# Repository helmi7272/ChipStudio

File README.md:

# ChipStudio
Графический инструмент проектирования ChipStudio. Новинки собственного производства Чип и Дип. 

Вам не хватает выводов GPIO для управления алгоритмами DSP, собранными в SigmaStudio? Или вы хотите, чтобы ресурсы звукового процессора не распылялись на кнопки, слайдеры или переключатели, а были сконцентрированы только на цифровой обработке аудио? А, может, мечтаете об одновременном управлении несколькими звуковыми процессорами и регулировке FIR-фильтров на лету? 
Обратите внимание на CHIP Studio!  
Интегрированная среда разработки CHIP Studio. Позволяет инженерам без опыта или с небольшим опытом написания программ для DSP процессоров добавлять любые функции внешней регулировки в свои проекты цифровой обработки сигналов. Это могут быть потенциометры, кнопки и переключатели.
CHIP Studio поддерживает все модули RDC2-0027, собранные на SigmaDSP процессоре ADAU1701, а также модуль SigmaDSP ADAU1761.
Этот инструмент поможет пользователям сократить время проектирования без ухудшения качества или характеристик.
Модуль RDC2-0051 предназначен для простого подключения внешних органов управления к проектам цифровой обработки звука созданных в <strong><em>Sigma Studio </em></strong>&ndash; среде разработки от компании Analog Devices. Код для любых функций модуля управления разрабатывается с помощью графического инструмента программирования <strong><em>CHIP Studio</em></strong>.<br />
Интегрированная среда разработки <strong><em>CHIP Studio </em></strong>v 0.0. Позволяет инженерам без опыта или с небольшим опытом написания программ для DSP процессоров добавлять любые функции внешней регулировки в свои проекты цифровой обработки сигналов. Это могут быть &nbsp;потенциометры, кнопки и переключатели.<br />
<strong><em>CHIP Studio </em></strong>поддерживает все модули RDC2-0027 собранные на SigmaDSP процессоре ADAU1701 и модуль SigmaDSP ADAU1761.<br />
Этот инструмент поможет пользователям сократить время проектирования без ухудшения качества или характеристик.<br />
<br />

<h2>Технические характеристики</h2>
Шины для управления DSP:<br />
<em>I2C x 2, SPI x 2</em><br />
Линий ввода/вывода&nbsp;- 10<br />
Функции линий ввода / вывода:<br />
<em>Кнопки/переключатели - 10</em><br />
<em>Переменные резисторы - 6</em><br />
На плате установлены:<br />
<em>Переменные резисторы &ndash; 2<br />
Кнопки &ndash; 2</em><br />
Питание &ndash; 5В внешнее или USB<br />
Размер платы: 100 мм х 34 мм
<h2>Схема</h2>
<p></p>

<h2>Назначение разъемов</h2>

<p></p>

<h2>Подключение ADAU1761</h2>
<p></p>
<h2>Подключение ADAU1701</h2>
<p></p>

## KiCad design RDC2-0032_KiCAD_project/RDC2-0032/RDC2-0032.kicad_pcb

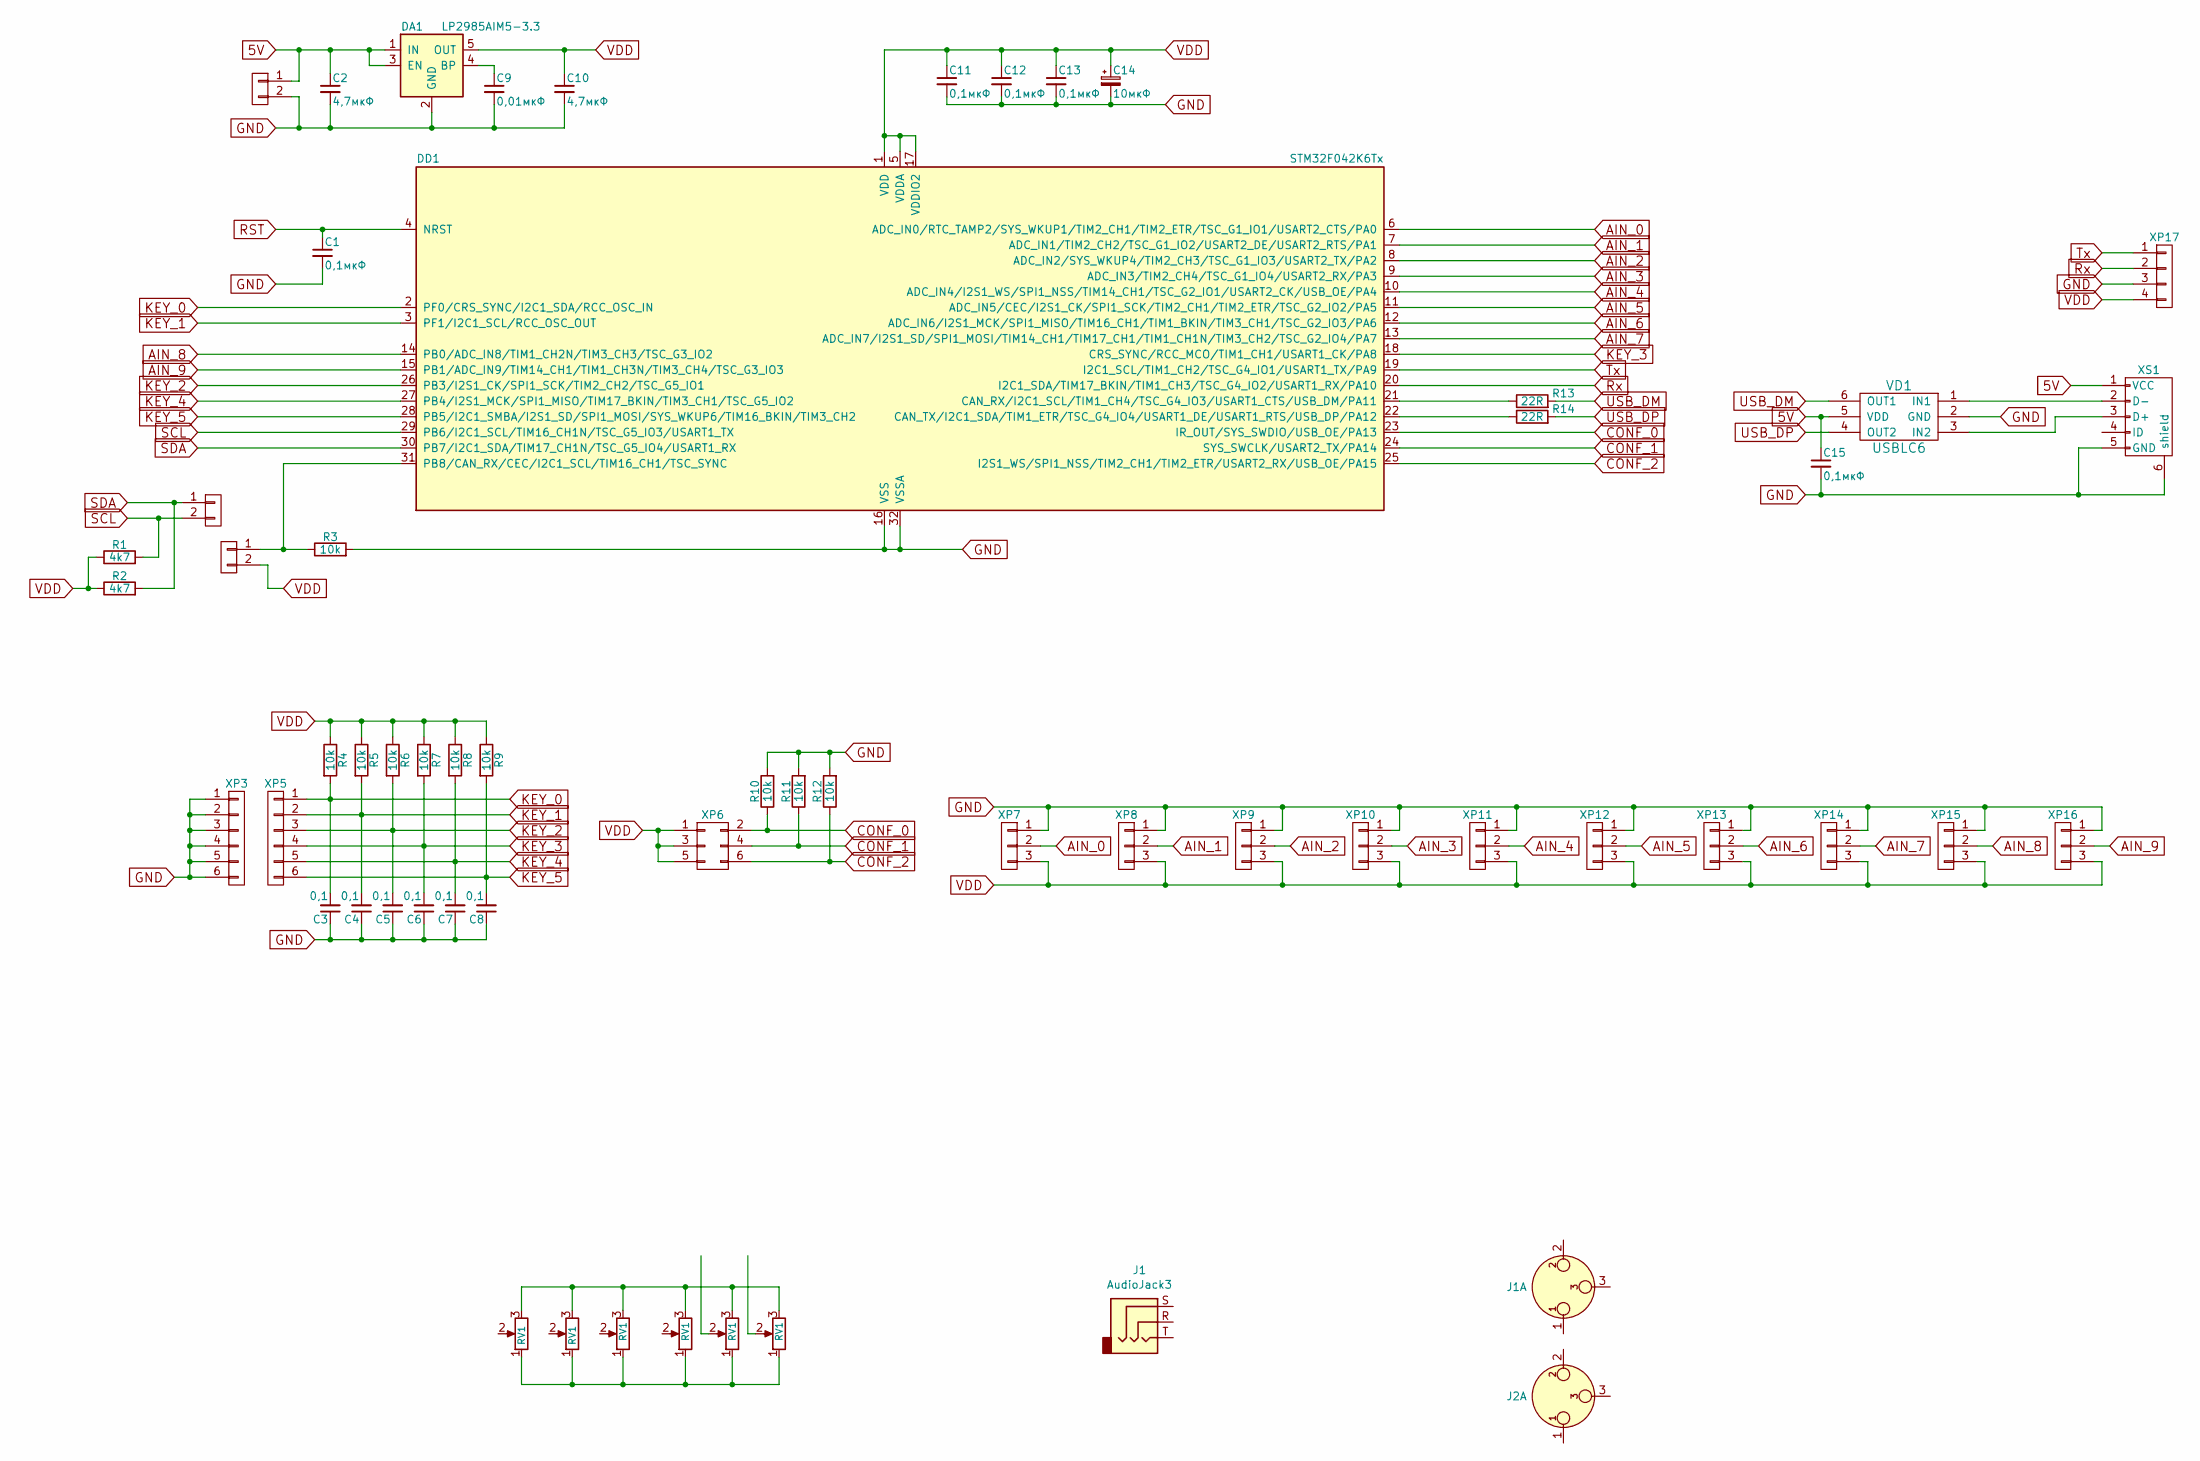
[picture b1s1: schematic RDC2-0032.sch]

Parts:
C1, C11, C12, C13, C15: 0,1мкФ; C_0603_HandSoldering
C2, C10: 4,7мкФ; C_0603_HandSoldering
C3, C4, C5, C6, C7, C8: 0,1; C_0603_HandSoldering
C9: 0,01мкФ; C_0603_HandSoldering
C14: 10мкФ; TantalC_SizeA_EIA-3216_HandSoldering_mm
DA1: LP2985AIM5-3.3; SOT-23-5_mm
DD1: STM32F042K6Tx; TQFP-32_7x7mm_Pitch0.8mm
J1: AudioJack3
J2: XLR3_AudioJack2_Combo
R1, R2: 4k7; R_0603_HandSoldering
R3, R4, R5, R6, R7, R8, R9, R10, R11, R12: 10k; R_0603_HandSoldering
R13, R14: 22R; R_0603_HandSoldering
VD1: USBLC6; SOT23-6L
XP1, XP2, XP4: PLS-2; Pin_Header_Straight_1x02_mm
XP3, XP5: CONN_01X06; Pin_Header_Straight_1x06_mm
XP6: CONN_02X03; Pin_Header_Straight_2x03_mm
XP7, XP8, XP9, XP10, XP11, XP12, XP13, XP14, XP15, XP16: CONN_01X03; Pin_Header_Straight_1x03_mm
XP17: CONN_01X04; Pin_Header_Straight_1x04_mm
XS1: USB_OTG; USB_Mini-B_mm

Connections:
5V: C2.1, C15.1, DA1.1 (IN), DA1.3 (EN), VD1.5 (VDD), XP4.1, XS1.1 (VCC)
AIN_0: DD1.6 (ADC_IN0/RTC_TAMP2/SYS_WKUP1/TIM2_CH1/TI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), XP7.2
AIN_1: DD1.7 (ADC_IN1/TIM2_CH2/TSC_G1_IO2/USART2_DE/U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), XP8.2
AIN_2: DD1.8 (ADC_IN2/SYS_WKUP4/TIM2_CH3/TSC_G1_IO3/U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), XP9.2
AIN_3: DD1.9 (ADC_IN3/TIM2_CH4/TSC_G1_IO4/USART2_RX/P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), XP10.2
AIN_4: DD1.10 (ADC_IN4/I2S1_WS/SPI1_NSS/TIM14_CH1/TSC_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), XP11.2
AIN_5: DD1.11 (ADC_IN5/CEC/I2S1_CK/SPI1_SCK/TIM2_CH1/T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), XP12.2
AIN_6: DD1.12 (ADC_IN6/I2S1_MCK/SPI1_MISO/TIM16_CH1/TI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), XP13.2
AIN_7: DD1.13 (ADC_IN7/I2S1_SD/SPI1_MOSI/TIM14_CH1/TIM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), XP14.2
AIN_8: DD1.14 (PB0/ADC_IN8/TIM1_CH2N/TIM3_CH3/TSC_G3_I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), XP15.2
AIN_9: DD1.15 (PB1/ADC_IN9/TIM14_CH1/TIM1_CH3N/TIM3_CH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), XP16.2
CONF_0: DD1.23 (IR_OUT/SYS_SWDIO/USB_OE/PA13), R10.1, XP6.2
CONF_1: DD1.24 (SYS_SWCLK/USART2_TX/PA14), R11.1, XP6.4
CONF_2: DD1.25 (I2S1_WS/SPI1_NSS/TIM2_CH1/TIM2_ETR/USAR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), R12.1, XP6.6
GND: C1.2, C2.2, C3.1, C4.1, C5.1, C6.1, C7.1, C8.1, C9.2, C10.2, C11.2, C12.2, C13.2, C14.2, C15.2, DA1.2 (GND), DD1.16 (VSS), DD1.32 (VSSA), R3.2, R10.2, R11.2, R12.2, VD1.2 (GND), XP3.1, XP3.2, XP3.3, XP3.4, XP3.5, XP3.6, XP4.2, XP7.1, XP8.1, XP9.1, XP10.1, XP11.1, XP12.1, XP13.1, XP14.1, XP15.1, XP16.1, XP17.3, XS1.5 (GND), XS1.6 (shield)
KEY_0: C3.2, DD1.2 (PF0/CRS_SYNC/I2C1_SDA/RCC_OSC_IN), R4.2, XP5.1
KEY_1: C4.2, DD1.3 (PF1/I2C1_SCL/RCC_OSC_OUT), R5.2, XP5.2
KEY_2: C5.2, DD1.26 (PB3/I2S1_CK/SPI1_SCK/TIM2_CH2/TSC_G5_IO1), R6.2, XP5.3
KEY_3: C6.2, DD1.18 (CRS_SYNC/RCC_MCO/TIM1_CH1/USART1_CK/PA8), R7.2, XP5.4
KEY_4: C7.2, DD1.27 (PB4/I2S1_MCK/SPI1_MISO/TIM17_BKIN/TIM3_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), R8.2, XP5.5
KEY_5: C8.2, DD1.28 (PB5/I2C1_SMBA/I2S1_SD/SPI1_MOSI/SYS_WKU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), R9.2, XP5.6
unnamed: C9.1, DA1.4 (BP)
unnamed: DD1.21 (CAN_RX/I2C1_SCL/TIM1_CH4/TSC_G4_IO3/USA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), R13.1
unnamed: DD1.22 (CAN_TX/I2C1_SDA/TIM1_ETR/TSC_G4_IO4/USA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), R14.1
unnamed: DD1.31 (PB8/CAN_RX/CEC/I2C1_SCL/TIM16_CH1/TSC_S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), R3.1, XP2.1
unnamed: VD1.1 (IN1), XS1.2 (D-)
unnamed: VD1.3 (IN2), XS1.3 (D+)
RST: C1.1, DD1.4 (NRST)
Rx: DD1.20 (I2C1_SDA/TIM17_BKIN/TIM1_CH3/TSC_G4_IO2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), XP17.2
SCL: DD1.29 (PB6/I2C1_SCL/TIM16_CH1N/TSC_G5_IO3/USAR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), R1.2, XP1.2
SDA: DD1.30 (PB7/I2C1_SDA/TIM17_CH1N/TSC_G5_IO4/USAR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), R2.2, XP1.1
Tx: DD1.19 (I2C1_SCL/TIM1_CH2/TSC_G4_IO1/USART1_TX/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), XP17.1
USB_DM: R13.2, VD1.6 (OUT1)
USB_DP: R14.2, VD1.4 (OUT2)
VDD: C10.1, C11.1, C12.1, C13.1, C14.1, DA1.5 (OUT), DD1.1 (VDD), DD1.5 (VDDA), DD1.17 (VDDIO2), R1.1, R2.1, R4.1, R5.1, R6.1, R7.1, R8.1, R9.1, XP2.2, XP6.1, XP6.3, XP6.5, XP7.3, XP8.3, XP9.3, XP10.3, XP11.3, XP12.3, XP13.3, XP14.3, XP15.3, XP16.3, XP17.4

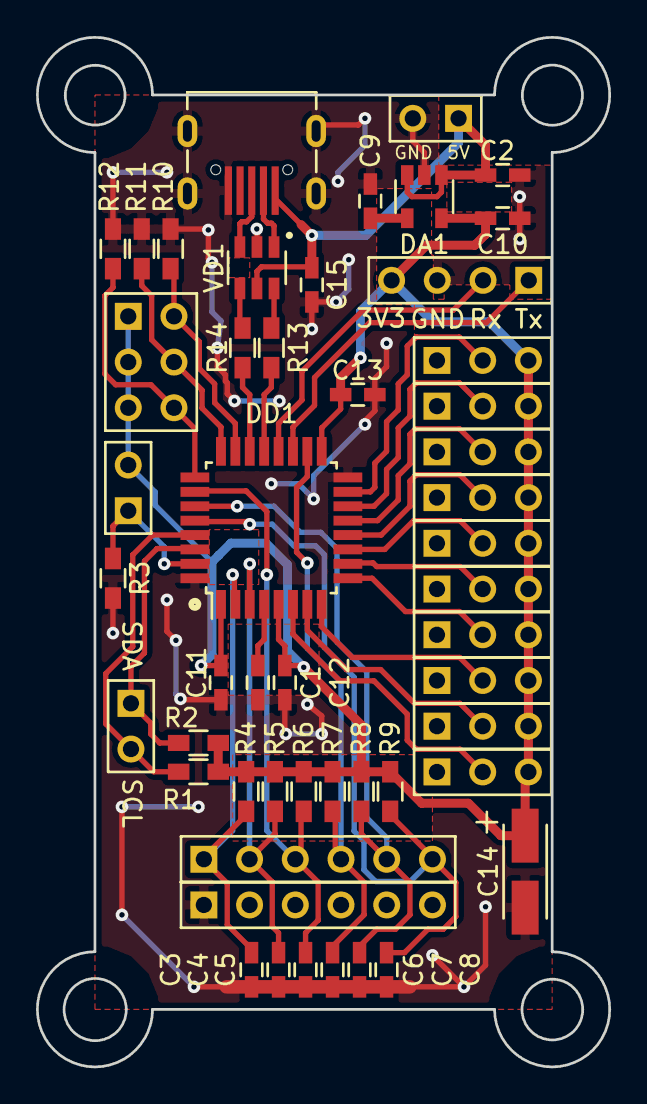
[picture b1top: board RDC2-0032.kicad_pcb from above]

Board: 2 copper layers, 31.8 x 57.2 mm, 50 parts (0 on the bottom side), 35 nets.

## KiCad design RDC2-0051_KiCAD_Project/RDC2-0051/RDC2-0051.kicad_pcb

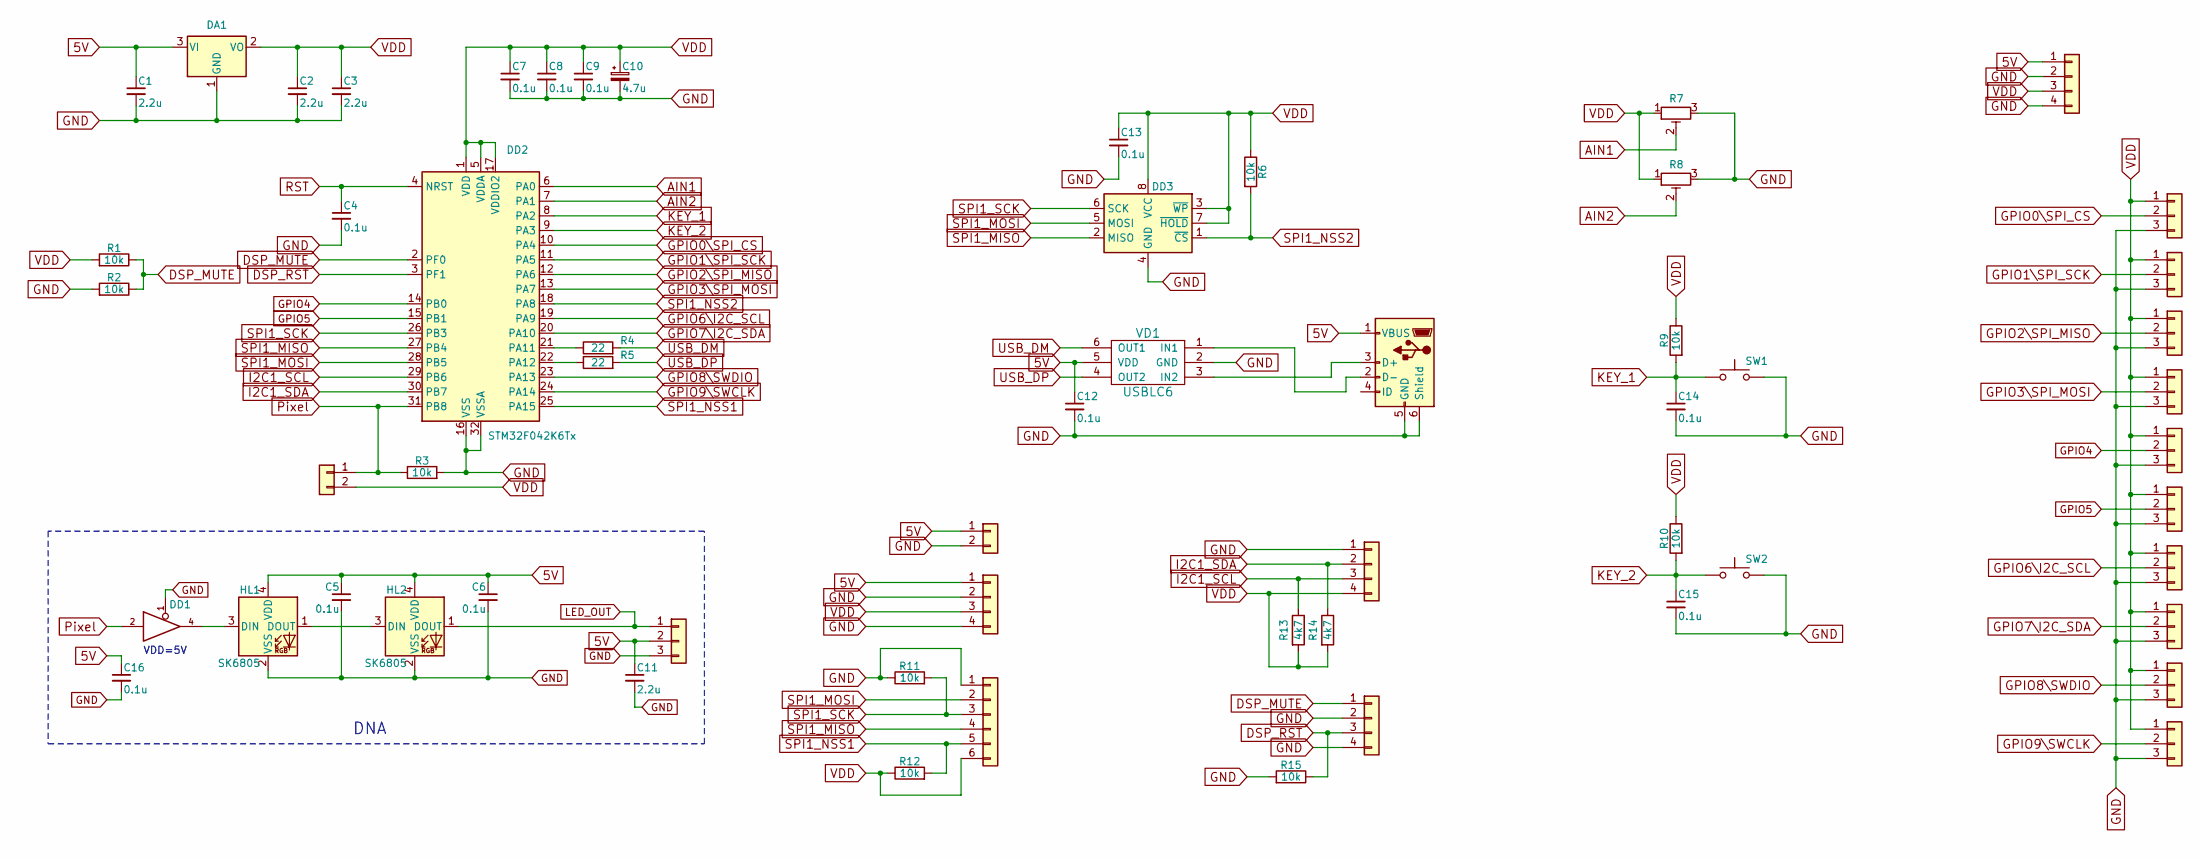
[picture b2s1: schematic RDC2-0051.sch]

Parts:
C1, C2, C3, C11: 2.2u; C_0603_HandSoldering
C4, C5, C6, C7, C8, C9, C12, C13, C14, C15, C16: 0.1u; C_0603_HandSoldering
C10: 4.7u; TantalC_SizeA_EIA-3216_mm
DA1: LM1117-3.3; SOT-223
DD1: 74AHC1G125; SOT-23-5_mm
DD2: STM32F042K6Tx; LQFP-32_7x7mm_Pitch0.8mm
DD3: 25LCxxx; SOIC-8_combo_Pitch1.27mm
HL1, HL2: SK6805; LED_SK6805_PLCC4_2.4x2.7mm_P1.3mm
R1, R2, R3, R6, R9, R10, R11, R12, R15: 10k; R_0603
R4, R5: 22; R_0603
R7, R8: R_POT_TRIM; R0904N
R13, R14: 4k7; R_0603
SW1, SW2: SW_PUSH; SW_PUSH_6mm_H13mm
VD1: USBLC6; SOT23-6L
XP1, XP3: Conn_01x02; Pin_Header_Straight_1x02_mm
XP2, XP11, XP12, XP13, XP14, XP15, XP16, XP17, XP18, XP19, XP20: Conn_01x03; Pin_Header_Straight_1x03_mm
XP4, XP6, XP7, XP8: Conn_01x04; Pin_Header_Straight_1x04_mm
XP5: Conn_01x06; Pin_Header_Straight_1x06_mm
XS1: USB_B_Micro; USB_micro_Molex_47346-0001

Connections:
5V: C1.1, C5.1, C6.1, C11.1, C12.1, C16.1, DA1.3 (VI), DD1.5 (VCC), HL1.4 (VDD), HL2.4 (VDD), VD1.5 (VDD), XP2.2, XP3.1, XP4.1, XP8.1, XS1.1 (VBUS)
AIN1: DD2.6 (PA0), R7.2
AIN2: DD2.7 (PA1), R8.2
DSP_MUTE: DD2.2 (PF0), R1.1, R2.1, XP7.1
DSP_RST: DD2.3 (PF1), R15.1, XP7.3
GND: C1.2, C2.2, C3.2, C4.2, C5.2, C6.2, C7.2, C8.2, C9.2, C10.2, C11.2, C12.2, C13.2, C14.2, C15.2, C16.2, DA1.1 (GND), DD1.1, DD1.3 (GND), DD2.16 (VSS), DD2.32 (VSSA), DD3.4 (GND), HL1.2 (VSS), HL2.2 (VSS), R2.2, R3.2, R7.3, R7.4, R8.3, R8.4, R11.1, R15.2, SW1.2, SW2.2, VD1.2 (GND), XP2.3, XP3.2, XP4.2, XP4.4, XP5.1, XP6.1, XP7.2, XP7.4, XP8.2, XP8.4, XP11.3, XP12.3, XP13.3, XP14.3, XP15.3, XP16.3, XP17.3, XP18.3, XP19.3, XP20.3, XS1.5 (GND), XS1.6 (Shield)
GPIO0\SPI_CS: DD2.10 (PA4), XP11.2
GPIO1\SPI_SCK: DD2.11 (PA5), XP12.2
GPIO2\SPI_MISO: DD2.12 (PA6), XP13.2
GPIO3\SPI_MOSI: DD2.13 (PA7), XP14.2
GPIO4: DD2.14 (PB0), XP15.2
GPIO5: DD2.15 (PB1), XP16.2
GPIO6\I2C_SCL: DD2.19 (PA9), XP17.2
GPIO7\I2C_SDA: DD2.20 (PA10), XP18.2
GPIO8\SWDIO: DD2.23 (PA13), XP19.2
GPIO9\SWCLK: DD2.24 (PA14), XP20.2
I2C1_SCL: DD2.29 (PB6), R13.1, XP6.3
I2C1_SDA: DD2.30 (PB7), R14.1, XP6.2
KEY_1: C14.1, DD2.8 (PA2), R9.2, SW1.1
KEY_2: C15.1, DD2.9 (PA3), R10.2, SW2.1
LED_OUT: HL2.1 (DOUT), XP2.1
unnamed: DD1.4, HL1.3 (DIN)
unnamed: DD2.21 (PA11), R4.1
unnamed: DD2.22 (PA12), R5.1
unnamed: HL1.1 (DOUT), HL2.3 (DIN)
unnamed: VD1.1 (IN1), XS1.2 (D-)
unnamed: VD1.3 (IN2), XS1.3 (D+)
Pixel: DD1.2, DD2.31 (PB8), R3.1, XP1.1
RST: C4.1, DD2.4 (NRST)
SPI1_MISO: DD2.27 (PB4), DD3.2 (MISO), XP5.4
SPI1_MOSI: DD2.28 (PB5), DD3.5 (MOSI), XP5.2
SPI1_NSS1: DD2.25 (PA15), R12.2, XP5.5
SPI1_NSS2: DD2.18 (PA8), DD3.1 (~CS), R6.2
SPI1_SCK: DD2.26 (PB3), DD3.6 (SCK), R11.2, XP5.3
USB_DM: R4.2, VD1.6 (OUT1)
USB_DP: R5.2, VD1.4 (OUT2)
VDD: C2.1, C3.1, C7.1, C8.1, C9.1, C10.1, C13.1, DA1.2 (VO), DA1.4, DD2.1 (VDD), DD2.5 (VDDA), DD2.17 (VDDIO2), DD3.3 (~WP), DD3.7 (~HOLD), DD3.8 (VCC), R1.2, R6.1, R7.1, R8.1, R9.1, R10.1, R12.1, R13.2, R14.2, XP1.2, XP4.3, XP5.6, XP6.4, XP8.3, XP11.1, XP12.1, XP13.1, XP14.1, XP15.1, XP16.1, XP17.1, XP18.1, XP19.1, XP20.1

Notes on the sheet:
VDD=5V
DNA

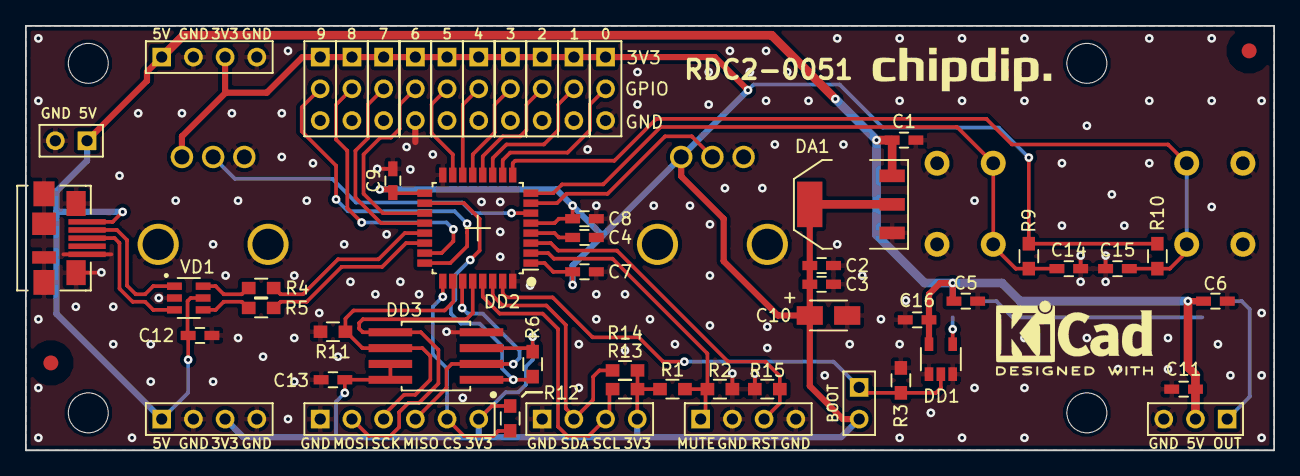
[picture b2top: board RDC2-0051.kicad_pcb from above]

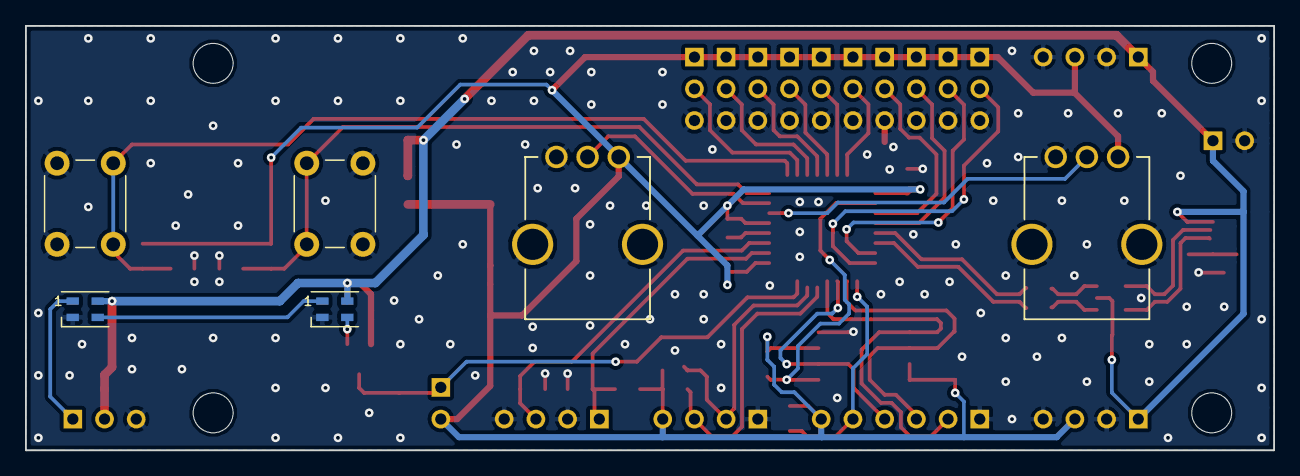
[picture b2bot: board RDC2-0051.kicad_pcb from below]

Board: 2 copper layers, 100.0 x 34.0 mm, 59 parts (6 on the bottom side), 37 nets.

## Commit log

2020-03-20 ADAU1761 ChipStudio project Vol, Bal, Mute, SuperB
2020-03-20 ChipStudio soft v3.0
2020-03-20 RDC2-0051 KiCAD project
2020-03-20 IAR Project
2020-03-20 firmware DFU v0.2
2020-03-20 FirmWare DFU
2020-03-27 ChipStudio soft v4.0
2020-03-27 firmware DFU v0.4
2020-03-27 ADAU1761 Vol, Bal, Mute, SuperB, Timbre
2020-04-04 firmware DFU v0.5
    v0.5
    - добавлена поддержка RDC2-0050 (TAS3251)
    - добавлена поддержка блоков схемы SigmaStudio, занимающих в памяти параметров DSP более 63 адресов (например, FIR-фильтры)
    - исправлена ошибка управления несколькими блоками DSP,
    подключенными к одной линии
2020-04-04 ChipStudio soft v5.0
    v0.5
    - добавлена поддержка RDC2-0050 (TAS3251)
    - добавлена поддержка блоков схемы SigmaStudio, занимающих в памяти параметров DSP более 63 адресов (например, FIR-фильтры)
    - исправлена ошибка управления несколькими блоками DSP,
    подключенными к одной линии
2020-05-10 ChipStudio v0.6
2020-05-10 RDC2-0032
2020-05-16 ChipStudio soft v0.7
2020-06-16 ChipStudio v0.9
2020-12-30 ChipStudio soft v0.94.3
